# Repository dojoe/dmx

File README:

Collection of my DMX512 related projects, mostly various
USB-DMX interfaces in varying levels of miniaturization.

interface/v1:
  My first Eagle-drawn DMX interface; all interfaces before
  it were made on breadboards. Features the famous FTDI FT232RL
  for USB-Serial conversion and a DS26C31 line driver.
  This is a "dumb" interface where the host needs to take
  care of the DMX protocol.

interface/v2:
  Still a dumb interface, but this one fits into a standard-
  issue XLR plug. Uses FT232RQ (same chip, smaller package)
  and a MAX485.

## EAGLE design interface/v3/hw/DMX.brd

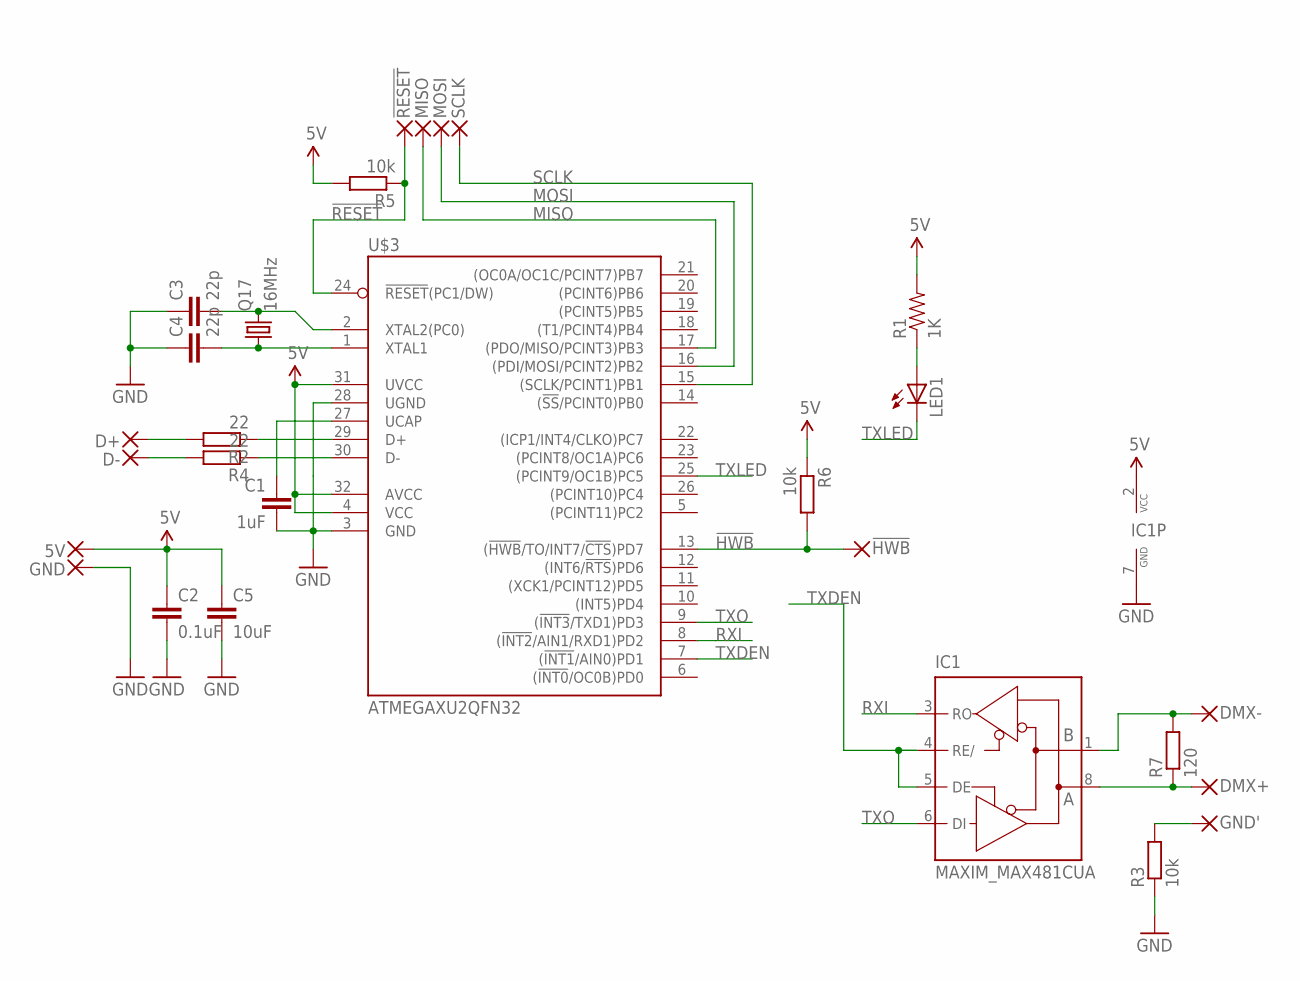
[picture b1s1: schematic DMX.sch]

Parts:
5V: WIREPAD2,15/1,0; 2,15/1,0
!HWB: WIREPADSMDCONTACT; SMDCONTACT
!RESET: WIREPADSMDCONTACT; SMDCONTACT
C1: 1uF; 0603-CAP
C2: 0.1uF; 0603-CAP
C3, C4: 22p; C0603
C5: 10uF; C0603K
D+: WIREPAD2,15/1,0; 2,15/1,0
D-: WIREPAD2,15/1,0; 2,15/1,0
DMX+: WIREPADSMD2,54-2,54; SMD2,54-2,54
DMX-: WIREPADSMD2,54-2,54; SMD2,54-2,54
GND: WIREPAD2,15/1,0; 2,15/1,0
GND': WIREPADSMD2,54-2,54; SMD2,54-2,54
IC1: MAXIM_MAX481CUA; MAXIM_UMAX8
LED1: LEDSML0805; SML0805
MISO: WIREPADSMDCONTACT; SMDCONTACT
MOSI: WIREPADSMDCONTACT; SMDCONTACT
Q17: 16MHz; TXC-7M
R1: 1K; 0603-RES
R2, R4: 22; R0603
R3, R5, R6: 10k; R0603
R7: 120; R0603
SCLK: WIREPADSMDCONTACT; SMDCONTACT
U$3: ATMEGAXU2QFN32; RHB_S-PQFP-N32

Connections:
5V: 5V.1, C2.1, C5.1, IC1.2 (VCC), R1.2, R5.2, R6.1, U$3.4 (VCC), U$3.31 (UVCC), U$3.32 (AVCC)
!HWB: !HWB.1, R6.2, U$3.13 ((!HWB!/TO/INT7/!CTS!)PD7)
!RESET: !RESET.1, R5.1, U$3.24 (!RESET!(PC1/DW))
DMX+: DMX+.1, IC1.8 (A), R7.1
DMX-: DMX-.1, IC1.1 (B), R7.2
GND: C1.2, C2.2, C3.1, C4.1, C5.2, GND.1, IC1.7 (GND), R3.1, U$3.3 (GND), U$3.28 (UGND)
GND': GND'.1, R3.2
MISO: MISO.1, U$3.17 ((PDO/MISO/PCINT3)PB3)
MOSI: MOSI.1, U$3.16 ((PDI/MOSI/PCINT2)PB2)
unnamed: LED1.A, R1.1
unnamed: C1.1, U$3.27 (UCAP)
unnamed: D+.1, R2.2
unnamed: D-.1, R4.2
unnamed: R2.1, U$3.29 (D+)
unnamed: R4.1, U$3.30 (D-)
unnamed: C3.2, Q17.B (2), U$3.2 (XTAL2(PC0))
unnamed: C4.2, Q17.A (1), U$3.1 (XTAL1)
RXI: IC1.3 (RO), U$3.8 ((!INT2!/AIN1/RXD1)PD2)
SCLK: SCLK.1, U$3.15 ((SCLK/PCINT1)PB1)
TXDEN: IC1.4 (RE/), IC1.5 (DE), U$3.7 ((!INT1!/AIN0)PD1)
TXLED: LED1.C, U$3.25 ((PCINT9/OC1B)PC5)
TXO: IC1.6 (DI), U$3.9 ((!INT3!/TXD1)PD3)

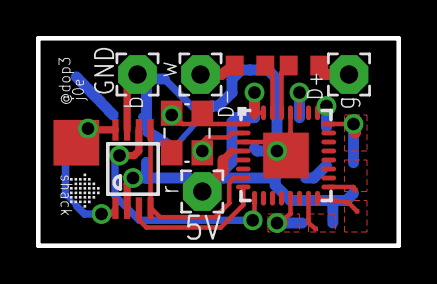
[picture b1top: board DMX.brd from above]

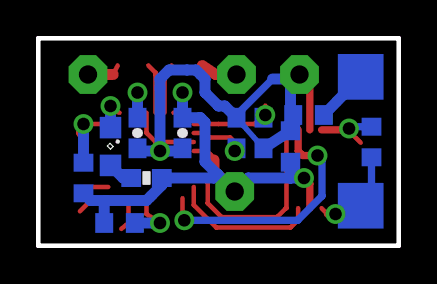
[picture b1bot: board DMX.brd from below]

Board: 2 copper layers, 20.0 x 11.5 mm, 28 parts (13 on the bottom side), 22 nets.

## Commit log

2012-01-12 Release v3 of the DMX interface, hardware only for starters
